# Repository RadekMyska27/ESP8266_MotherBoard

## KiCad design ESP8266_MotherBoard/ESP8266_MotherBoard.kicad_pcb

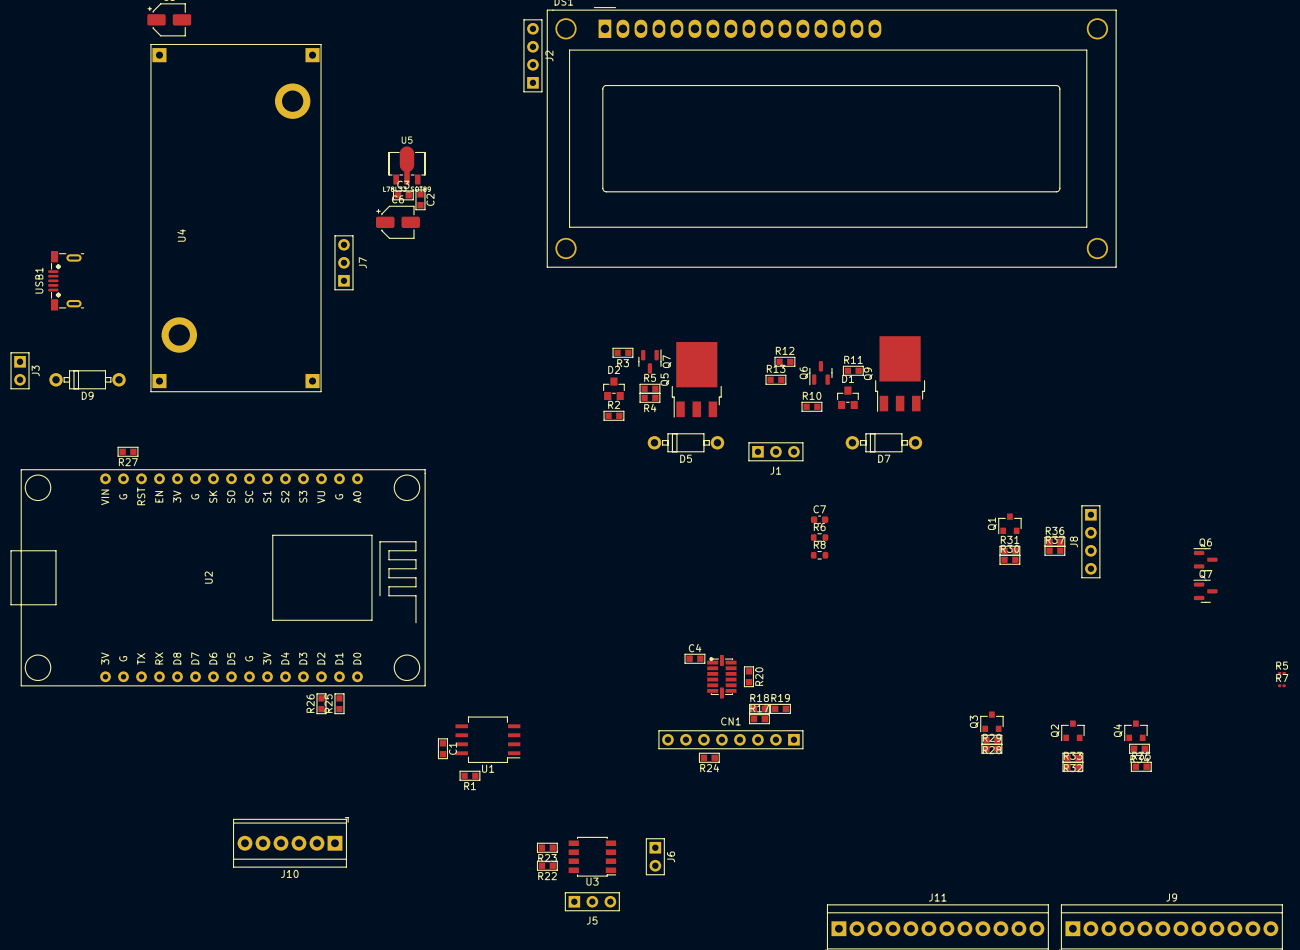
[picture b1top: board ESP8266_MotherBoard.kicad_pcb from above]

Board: 2 copper layers, 74 parts (0 on the bottom side), 56 nets, no tracks yet.

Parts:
C1, C3, C4: CERAMIC-100NF-50V-10%-X7R_0603_; C0603
C2: CERAMIC-300NF-50V-10%-X7R_0603_; C0603
C5, C6: TANTALUM-SMD-10UF-10V-10%_AVX-A_; CP_Elec_4x5.4
C7: CERAMIC-100NF-50V-10%-X7R_0603_; C_0603_1608Metric
CN1: DIP-BLACK-FEMALE-HEADER-VERT_8P-2.54_; H8-2.54
D1, D2: BZX84C15BS; SOT-23
D5, D7, D9: 1N4001; DO-41
DS1: WC1602A
IC1: ADXL345; ADXL3x5
J1: Screw_Terminal_01x03; H3-2.54
J2: DIP-BLACK-MALE-HEADER-VERT_4P-2.54_; H4-2.54
J3, J6: Screw_Terminal_01x02; H2-2.54
J5, J7: DIP-BLACK-MALE-HEADER-R_A_3P-2.54-90D_; H3-2.54
J8: DIP-BLACK-FEMALE-HEADER-VERT_4P-2.54_; H4-2.54
J9, J11: Screw_Terminal_01x12; TerminalBlock_TE_1-282834-2_1x12_P2.54mm_Horizontal
J10: Screw_Terminal_01x06; TerminalBlock_TE_282834-6_1x06_P2.54mm_Horizontal
Q1, Q2, Q3, Q4, Q6, Q7: MMBT2907; SOT-23
Q5, Q9: IRF9630; TO-252-3_TabPin4
Q6#2, Q7#2: BC849; SOT-23
R1, R4, R5, R12, R13, R17, R18, R19, R20, R22, R23, R24, R25, R26, R27, R29, R30, R31, R32, R33, R34, R35: SMD-RES-10K-1%-1_10W_0603_; R0603
R2, R10: SMD-RES-10K-5%-1_10W_0603_; R0603
R3, R11: SMD-RES-1k5-5%-1_10W_0603_; R0603
R5#2, R7: SMD-RES-10K-1%-1_10W_0603_; R_0201_0603Metric
R6, R8: OPL_Resistor_SMD-RES-2.2K-5%-1_10W_0603_; R_0603_1608Metric
R28: 10k; R0603
R36: SMD-RES-1K-5%-1_10W_0603_; R0603
R37: SMD-RES-2K-5%-1_10W_0603_; R0603
U1: LM75B; SO-8_5.3x6.2mm_P1.27mm
U2: NodeMCU1.0(ESP-12E); NodeMCU1.0(12-E)
U3: L9110; SSOP-8_3.95x5.21x3.27mm_P1.27mm
U4: XL6009_Module; xl6009_footPrint
U5: L78L33_SOT89; SOT-89
USB1: MICRO-USB-SMD-B-_10118193-0001LF_; MICRO-USB5+4P-SMD-0.65-B

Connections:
+3V3: C3.1, C4.2, C6.1 (+), CN1.2, IC1.1 (VDD_IO), IC1.6 (Vs), Q2.2 (E), Q3.2 (E), Q4.2 (E), R17.1, R18.1, R19.2, R25.1, R26.1, R27.2, R28.1, R32.1, R34.1, U5.1 (OUT)
+5V: C1.2, C2.1, C7.2, J2.1, J5.1, J7.2, Q1.2 (E), R1.2, R30.1, U1.8 (+Vs), U2.15 (VIN), U5.3 (IN)
+12V: D1.1 (K), D2.1 (K), D9.1 (K), J5.3, Q5.3 (S), Q9.3 (S), R2.1, R5.1, R10.1, R13.1, U4.1 (IN_BAT)
Analog_input: J9.1, U2.1 (A0(ADC0))
CLK: J11.4, U2.9 (CLK(SCLK))
CS: J11.2, U2.7 (CMD(CS))
EN: J9.12, U2.12 (EN)
GND: C1.1, C2.2, C3.2, C4.1, C5.2 (-), C6.2 (-), C7.1, CN1.1, D5.2 (A), D7.2 (A), IC1.2 (GND), IC1.4 (GND), IC1.5 (GND), J1.3, J2.2, J8.2, J10.2, J10.4, J10.6, J11.11, Q6.3 (C), Q6#2.2 (E), Q7.3 (C), Q7#2.2 (E), R5#2.1, R6.1, R7.1, R8.1, R20.2, R24.1, R37.2, U1.4 (GND), U1.5 (A2), U1.6 (A1), U1.7 (A0), U2.10 (GND), U2.14 (GND), U2.17 (GND), U2.24 (GND), U3.5 (GND), U3.8 (GND), U4.4 (OUT_GND), U5.2 (GND), USB1.5 (GND), USB1.6 (GND), USB1.7 (GND), USB1.8 (GND), USB1.9 (GND)
GPI_1: J11.5, U2.23 (D5(GPIO14))
GPI_2: J11.6, U2.22 (D6(GPIO12))
GPI_3: J11.7, U2.30 (D0(GPIO16))
GPO_1: J11.8, Q3.3 (C)
GPO_2: J11.9, Q2.3 (C)
GPO_3: J11.10, Q4.3 (C)
H_bridge_IA: R23.1, U3.6 (IA)
H_bridge_IB: R22.1, U3.7 (IB)
MCU_GPO_1: J9.2, R29.2, U2.21 (D7(GPIO13))
MCU_GPO_2: J9.3, R33.2, U2.20 (D8(GPIO15))
MCU_GPO_3: J9.4, R35.2, U2.4 (SD3(GPIO10))
MCU_GPO_4: J9.5, R31.2, U2.5 (SD2(GPIO9))
MCU_PWM_1: J9.6, R4.1, R8.2, U2.27 (D3(GPIO0))
MCU_PWM_2: J9.7, R6.2, R12.1, U2.26 (D4(GPIO2))
MISO: J11.3, U2.8 (SDO(MISO))
MOSI: J11.1, U2.6 (SD1(MOSI))
unnamed: C5.1 (+), J7.3, U4.3 (OUT_+)
unnamed: CN1.6, R24.2
unnamed: D1.2 (A), Q9.1 (G), R10.2, R11.2
unnamed: D2.2 (A), Q5.1 (G), R2.2, R3.2
unnamed: D9.2 (A), J3.2
unnamed: IC1.7 (CS), R19.1
unnamed: IC1.8 (INT1), R17.2
unnamed: IC1.9 (INT2), R18.2
unnamed: IC1.12 (SDO), R20.1
unnamed: J3.1, U4.2 (IN_GND)
unnamed: J5.2, R22.2, R23.2, U3.2 (VCC), U3.3 (VCC)
unnamed: J6.1, U3.4 (OB)
unnamed: J6.2, U3.1 (OA)
unnamed: J7.1, USB1.1 (VCC)
unnamed: J8.1, Q1.3 (C)
unnamed: J8.4, R36.1, R37.1
unnamed: Q1.1 (B), R30.2, R31.1
unnamed: Q2.1 (B), R32.2, R33.1
unnamed: Q3.1 (B), R28.2, R29.1
unnamed: Q4.1 (B), R34.2, R35.1
unnamed: Q6.1 (B), Q6#2.1 (B), R5#2.2, R12.2, R13.2
unnamed: Q6#2.3 (C), R11.1
unnamed: Q7.1 (B), Q7#2.1 (B), R4.2, R5.2, R7.2
unnamed: Q7#2.3 (C), R3.1
unnamed: R1.1, U1.3 (O.S.)
PWM__toLoad_1: D5.1 (K), J1.1, Q5.2 (D)
PWM__toLoad_2: D7.1 (K), J1.2, Q9.2 (D)
RST: R27.1, U2.13 (RST)
Rx: J8.3, J9.10, U2.19 (RX(DPIO3))
SCL: CN1.8, IC1.14 (SCLK), J2.4, J9.8, R25.2, U1.2 (SCL), U2.29 (D1(GPIO5))
SDA: CN1.7, IC1.13 (SDI), J2.3, J9.9, R26.2, U1.1 (SDA), U2.28 (D2(GPIO4))
Tx: J9.11, R36.2, U2.18 (TX(GPIO1))

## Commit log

2021-08-07 test branch sch and board changed
2021-08-07 added D3 ro PWM modul
2023-11-06 pwm module corrections and simulations LTS
